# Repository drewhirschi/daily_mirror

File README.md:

# Daily Mirror

Daily Mirror is a small physical camera appliance: press one button, take one
photograph, and upload it to a private chronological gallery.

The current revival keeps the interaction deliberately narrow. There is no
identity recognition, comparison, notes, alignment, or time-lapse generation.

## Repository layout

- `mobile/` — native Expo iOS gallery and account app, with a persistent,
  bounded thumbnail cache. See [`docs/mobile.md`](docs/mobile.md).
  For remote iPhone builds and installation, see the
  [free Tailscale/Xcode bridge guide](docs/tailscale-xcode-bridge.md).
- `packages/api/` — portable TypeScript API client with types generated from
  the Rust server's OpenAPI contract.
- `device/` — new Rust Raspberry Pi client: camera command, GPIO button and
  three LEDs, durable upload queue, and retries.
- `server/` — new NextRS/Axum API, local filesystem storage, React gallery,
  and Docker Compose configuration.
- `processor/` — intermittent Rust face-processing CLI and leased batch runner;
  the inference adapter is intentionally pending model selection.
- `crates/vision-contract/` — shared queue and face-result wire types used by
  the server and processor.
- `src/`, `snapr/`, and `view/` — the original 2022 Python, Rust/OpenCV, and
  React prototypes retained for reference.
- `data/` — photographs and face-recognition experiments from the original
  prototype. New captures do not belong in Git.

## Prototype flow

```text
button -> LED countdown -> ArduCam JPEG -> durable Pi queue
       -> signed upload grant -> local storage or private R2 -> web gallery
```

The device writes a completed JPEG to its queue before uploading. It removes
that file only after the server acknowledges it. A stable capture ID makes
network retries idempotent.

## Start the web server

```sh
cd server
cp .env.example .env
npm install
npm run client:generate
cargo dev
```

See `server/README.md` for the upload API and container setup.

The password-protected production gallery is deployed at
<https://daily-mirror-pearl.vercel.app>.

The planned path from breadboard prototype to an enclosed Pi appliance, R2 and
Vercel deployment, and a later ESP32 port is documented in
[`docs/productization-plan.md`](docs/productization-plan.md).
Deployment commands and the direct-to-R2 upload flow are documented in
[`docs/deployment.md`](docs/deployment.md).
The local Rust processing worker, durable job queue, face landmarks, identity
review workflow, and centered portrait pipeline are documented in
[`docs/face-processing-architecture.md`](docs/face-processing-architecture.md).

## Bring up the Raspberry Pi camera

```sh
cd device
cp .env.example .env
cargo run --release -- capture-once --no-upload
```

After validating the ArduCam output, configure the server URL and test an
upload before wiring GPIO. See `device/README.md` for pin assignments and LED
behavior.

## Inspect the face-processing queue

After setting `DAILY_MIRROR_SERVER_URL`, `DAILY_MIRROR_PROCESSOR_TOKEN`, and
`DAILY_MIRROR_PROCESSING_PIPELINE` in `processor/.env`, run:

```sh
just process-status
```

The leased Rust processing loop is implemented, but `just process` will refuse
to claim production photos until a face inference engine is selected. See
[`processor/README.md`](processor/README.md) and the
[face-processing architecture](docs/face-processing-architecture.md).

## Quality gates

Run `just check` to format-check, lint, generate and validate the typed client,
type-check the gallery, and test all Rust applications. Run
`just install-hooks` once per clone to make the same suite a mandatory local
pre-push hook. GitHub Actions runs it again for every push and pull request,
and production deployment refuses to start until it passes.

The root npm workspace manages mobile and shared TypeScript packages; the
NextRS server keeps its existing generated-client workspace. Run `npm ci` at
the repository root to install mobile dependencies, then `npm run mobile` for
Metro or `npm run ios` on a Mac to build and open the simulator.

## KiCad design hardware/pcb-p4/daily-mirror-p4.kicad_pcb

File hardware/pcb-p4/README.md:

# Daily Mirror custom PCB - A1 component study

Open **daily-mirror-p4.kicad_pro** in KiCad 10. This is an editable starting
project with the connected controls schematic and **64 additional candidate
components** on four new schematic pages and the board. It now has 80 electrical
references plus four mounting holes. The imported main components have no circuit
connections yet; the board has no routed traces. **Do not order this board.**

See [sourcing.md](sourcing.md) for the part choices, 3D-model limitations and
open-reference workflow. [candidate-parts.csv](candidate-parts.csv) records
the new parts and their sources; it is not an order-ready BOM.

An editable, routed Olimex P4 development-board reference is in
[reference/olimex-esp32-p4-devkit](reference/olimex-esp32-p4-devkit).
Open its `ESP32-P4-DevKit_Rev_D1.kicad_pro` separately to inspect the original
connected design. It has not been merged into the Daily Mirror circuit.
The previous A0 files/previews are saved in `revisions/a0`.

## Decisions from this session

- Keep the existing Arducam IMX519 as the camera baseline; preserve the goal of
  16 MP stills. Use a purchased camera module on a ribbon cable. The image
  sensor and lens do not need to be integrated onto the main custom PCB.
- USB-C wall power; a new enclosure designed around the final electronics.
- Cost matters: favor a standard four-layer main board for the P4, common
  stocked components, and assembly on one side where practical. Evaluate total
  assembled cost, including setup and shipping, rather than promotional bare-PCB
  prices. No per-unit budget or production quantity has been specified yet.
- One small four-pin RGB status indicator, plus a momentary capture/pairing button.
- **White-only emitters are preferred** around the perimeter for photographs.
  The three-color CL651-3S modules are optional prototype parts, not a required
  final component. Choose documented white LEDs/modules and their current
  drivers once the brightness, optical layout and power budget are established.
- Snap-in removable diffuser above the light modules. Include an opaque lens
  baffle, room between diffuser and emitters, and space behind the modules for
  a heat-spreading mount. Diffuser material, thickness, gap and clips need an
  optical/mechanical prototype; the current enclosure models are Pi-specific.

## Important processor finding

**The ESP32-P4 is still a candidate, not a confirmed solution for full-resolution
IMX519 capture.** Having a matching MIPI interface does not establish camera support.

Espressif's current ISP header defines `ISP_LL_HSIZE_MAX` as **1920**. Its ISP
driver rejects larger `h_res` values. The IMX519 full image is **4656 x 3496**.
Thus the ordinary P4 ISP processing path cannot process a full-width 16 MP frame.
This is an image-processing-path limit, not proof that every raw CSI/DMA capture
path is impossible. A bypass-and-upload approach would need a sensor driver,
working DMA/buffer handling, exposure/focus control and a server image pipeline.
It has not been implemented or tested here.

The official sensor list does not list a native IMX519 driver. Its Arducam
PIVARIETY entry does not establish support for the user's native IMX519 module.
The community IMX driver project checked lists other IMX sensors, not IMX519;
its results cannot be assumed to apply to this camera.

A packed RAW10 full frame is 20,346,720 bytes (19.40 MiB); a 16-bit-per-pixel
buffer takes 32,554,752 bytes (31.05 MiB), before firmware and other buffers.
Capturing infrequently reduces average throughput, but not those per-frame
buffer requirements. Streaming approaches must be proven separately.

**Next hardware gate:** demonstrate a full-field still from the actual IMX519
on the proposed processor, with usable exposure/focus and successful upload.
If P4 raw capture cannot meet that requirement, select a processor with a
validated IMX519 pipeline before drawing its main circuit. A custom board
does not require a Raspberry Pi, and a P4 has not been chosen merely for size.

Source snapshot: ESP-IDF commit `c712a0dde385d659a1470a136251980d31a70bc1`,
checked September 14, 2026. See [reference/isp-limits.md](reference/isp-limits.md).

## What is actually drawn

| Reference | Circuit | Current choice |
| --- | --- | --- |
| D1 | Common-anode RGB indicator | Project symbol preserves documented pin order: 1 blue, 2 green, 3 common positive, 4 red |
| R1-R3 | One current-limiting resistor per color | 1 kohm provisional; adjust after measuring forward voltage and brightness |
| R5-R7 | Pull each color control high while GPIO is floating | 100 kohm; high = off, low = on |
| SW1 | Normally-open momentary button | Generic 6 mm tactile footprint, 4.3 mm actuator height candidate |
| R4 / C1 | Button pull-up and filter | 10 kohm / 100 nF; approximately 1 ms RC; use firmware debounce as well |
| TP1-TP6 | Future processor/control test access | 3.3 V, ground, blue, green, red, button |
| H1-H4 | Board-only mounting holes | M3 clearance, provisional 92 x 92 mm spacing |

The LED's common positive leg has **no fourth series resistor**. Three separate
color resistors avoid the brightness interactions caused by sharing one resistor.
The 1 kohm starting values cap direct GPIO current below 3.3 mA per channel at
3.3 V; final brightness, GPIO limits and resistor power must be checked against
the chosen parts. This is only the small indicator circuit, not the COB driver.

The RGB symbol follows [the existing wiring record](../../device/README.md),
but the loose LED's view/orientation, lead size and lead order must be confirmed.
The candidate **wide-pin** footprint uses formed leads at 2.54 mm pitch; it is
not a claim that the unbent loose LED has that pitch. The generic button's
mechanical height must also be chosen with the new faceplate.

The board is a **100 x 100 mm, four-copper-layer space study**. None of those
dimensions, mounting holes or layer rules is a final manufacturing specification.
The PCB now contains the imported candidate footprints, including eight white
emitters. The camera faceplate clearance is still a drawing guide; the separate
camera module, cable, diffuser and enclosure have not been mechanically modeled.
The 3D preview represents these placed components; five package types use explicitly
approximate models. See the sourcing notes before using this for mechanical fit.

## Existing CL651-3S prototype light modules

The final board can use white-only parts instead. The notes below apply only
if the already-owned three-color modules are used for prototype measurements.

The supplied photo and the manual linked from the exact
[Temu listing](https://www.temu.com/goods.html?goods_id=606385509136562&sku_id=99388093393455)
identify a three-color, common-negative COB module. The manual explicitly maps:

| Pad marking | Seller's stated function |
| --- | --- |
| `B+` | White positive |
| `W+` | Blue positive |
| `R+` | Red positive |
| `-` | Shared negative |

This unusual B/W assignment should be checked at low current on a current-limited
bench supply before wiring a batch. Only white and negative will be used;
unused red/blue positives stay unconnected.

The listing/manual states **3.2-3.7 V** and warns of heating at 3.7 V. It provides
**no rated current, pulse current, pulse width, thermal resistance, CRI or CCT**.
It is not a complete electrical datasheet. Do not substitute its broad listing
category `<=36 V` for the actual operating voltage.

Plan a controlled-current path for each white module, with default-off enable
and a bounded illumination time. Do not drive COB modules from GPIO, connect
them directly to USB's 5 V, or infer a current limit from voltage alone. Do not
parallel bare modules behind one driver without a validated current-sharing scheme.
The appropriate buck/linear topology, current sense resistor, module count,
connector, copper area and USB supply rating remain unresolved.

These parts already have their own substrate. The likely integration is short
two-wire connections to modules mounted around the faceplate/perimeter, with
control electronics on the main PCB. Direct mechanical/electrical attachment
to the main board needs measured pad positions, mounting holes and a thermal
design. No guessed CL651-3S solder footprint is included.

### Flash timing and diffuser

Short duty cycles reduce average heat: `average electrical power = V * I *
on-time * flashes-per-second` for constant rectangular pulses. Peak junction
temperature and safe pulse current still matter; average power alone does not
establish safety. Repeated presses and a stuck-on software state must be tested.
No pulse overdrive is assumed without a manufacturer rating.

The IMX519 is a rolling-shutter camera. Start with steady white illumination
through the full frame exposure/readout window, then characterize the shortest
uniform pulse from actual captured images. Avoid unsynchronized PWM during
capture. Test for bands, face shadows, clipping, diffuser hot spots, lens flare
and enclosure temperature at the maximum intended repeat rate.

Record current, measured light output and duration before deciding whether a
small heat spreader is enough. Keep diffuser clips clear of the thermal path.

## What the main circuit still needs

- Camera-proven processor, package/revision and memory capacity.
- For a P4 design: external flash, reference crystal, core regulator, PHY and
  other supplies/decoupling, reset/boot circuitry and programming access. Use
  Espressif's revision-v3-or-later reference; older revisions differ electrically.
- Wi-Fi/BLE companion and antenna layout if using P4. ESP32-C6-MINI-1 with SDIO
  is the reference direction; P4 itself does not contain a Wi-Fi/BLE radio.
- USB-C connector, CC handling, input protection, regulator and current budget.
  Two CC pull-downs establish a sink attachment but do not by themselves authorize
  a 3 A load. Detect the source's available current or negotiate PD as required.
- Exact Arducam module SKU/revision and ribbon. Pi-style connectors can be 15-pin
  1 mm or 22-pin 0.5 mm. Confirm connector-side pin numbering, contacts, supply,
  controls, level shifting and cable orientation before assigning the footprint.
- CSI differential pairs routed against the chosen fabricator's stackup and
  Espressif's guidelines; impedance is not established by arbitrary trace widths.
- Flash/illumination driver and any local storage required for failed uploads.

The phone experience is firmware/app work too: BLE discovery while pairing,
authenticated ownership setup, transfer of Wi-Fi credentials, association and
account registration, then normal capture/upload. Add long-press recovery,
factory reset, signed updates and upload retry. KiCad does not implement this.
The existing Pi program invokes `rpicam-still`; that part cannot run unchanged
on the P4. Backend protocols and device states can be reused where applicable.

## KiCad setup and working together

KiCad **10.0.6** was installed without its library packages. The matching official
Arch packages (`kicad-library` and `kicad-library-3d`, 10.0.6-1) were downloaded,
their signatures verified against the installed Arch keyring, and extracted to:

`/home/drew/.local/share/kicad/10.0/official-10.0.6`

This per-user install avoids the system installer's password requirement. It
does not register those two library packages with pacman. KiCad's global library
table references and `KICAD10_*` paths were updated. The previous settings are in:

`/home/drew/.config/kicad/10.0/before-daily-mirror-20260914-214132`

The dangling default reference to a nonexistent optional design-block library
was also removed; its original table is in that backup. Design blocks are not
needed for this project.

Restart KiCad once if it was already open. Then:

1. **File > Open Project** and select `daily-mirror-p4.kicad_pro` in this directory.
2. Open the `.kicad_sch` for the architecture and control circuit.
3. Open the `.kicad_pcb`; enable `User.Drawings` to see the reserved areas.
4. Use **View > 3D Viewer** to inspect the placed candidate parts.

The current 3D render is `output/board-3d.png`. The STEP assembly in
`output/daily-mirror-a0.step` contains the current board and the placed component
models, and can be opened in mechanical CAD for enclosure work. Neither includes
the unselected processor, camera module, power connectors or white emitters.

### Reading the design

The schematic describes electrical connections. Green lines are wires in that
diagram; repeated net names identify the same electrical connection without
drawing a long line across the page. The PCB shows real component locations and
solder pads. Its connections become copper **traces** routed between pads;
this initial board has no routed traces yet. In the PCB editor, thin ratsnest
lines can show which pads still need connections; those are guides, not copper.
The 3D viewer shows physical models, not schematic symbols or ratsnest lines.

| Label | Meaning |
| --- | --- |
| J1, J2 | Connectors, such as camera ribbon or USB |
| U1, U2 | Integrated circuits/chips; exact function depends on the part |
| R1, R2 | Resistors |
| C1, C2 | Capacitors; often resemble tiny resistors |
| D1 | Diode or LED |
| SW1 | Switch/button |
| TP1 | Test point |

For a sourced part, check three separate CAD representations: its schematic
symbol (electrical pins), footprint (solder pads and holes), and STEP/3D model
(physical shape). Matching physical shape alone does not prove the pin mapping
or circuit works. Use exact manufacturer part numbers and package drawings.

### Making a physical unit

PCB fabrication makes the patterned copper board. PCB assembly adds and solders
the purchased components. An assembly order typically needs Gerbers/drill files,
a bill of materials with exact part numbers, and placement/orientation data.
Fabricators do not print silicon image sensors or lenses. A camera module can
be purchased separately and connected after board assembly.

JLCPCB offers an assembly parts library and sourcing/consignment options;
PCBWay offers turnkey, partial-turnkey and customer-supplied component assembly.
Stock, exact packages and service eligibility must be checked before choosing
the final bill of materials. Firmware flashing and functional testing require
their own agreed process; soldering the board does not establish that it works.

- [DigiKey CAD models](https://www.digikey.com/en/product-highlight/a/accelerated-designs/ultra-librarian)
- [KiCad 10 PCB and 3D documentation](https://docs.kicad.org/10.0/en/pcbnew/pcbnew.html)
- [JLCPCB bill of materials requirements](https://jlcpcb.com/help/article/bill-of-materials-for-pcb-assembly)
- [JLCPCB parts sourcing](https://jlcpcb.com/help/article/how-to-build-your-own-parts-library-in-jlcpcb)
- [PCBWay component sourcing](https://www.pcbway.com/pcb_prototype/Electronic_Components.html)

There is no callable KiCad MCP in this session. We can edit the native files
and use KiCad CLI for validation and previews. Close the affected editor before
external edits and reopen it afterward; do not assume live reload. For edits
made in the schematic editor, **Update PCB from Schematic (F8)** transfers changes.
The `.kicad_pro` file is the project, `.kicad_sch` is the circuit, and
`.kicad_pcb` is the physical board.

Small project-local symbol, footprint and 3D libraries make the study portable.
The generator refuses to overwrite an existing design. Interactive KiCad files
are the source of truth once editing begins. To reproduce the initial study in
a separate directory:

```sh
python build_starter.py --output /tmp/daily-mirror-pcb-study
```

## Checks

See [output/validation.json](output/validation.json) for the final counts.
The controls schematic still has zero ERC violations and its nine nets match
the board pads. All 80 schematic component pin-number sets match the footprints,
with J2's additional mechanical mounting tabs explicitly accounted for. All 74
placed model references resolve. No component courtyards overlap.

The whole project has **377 ERC findings** from unconnected/undriven candidate
pins and **96 DRC findings** (USB pad nets/connector hole clearance and silkscreen
size/overlaps). The 21 unrouted controls connections remain; because the new
circuits have no assigned nets, that number does not count their future routing.
No Daily Mirror Gerbers, assembly order or firmware release has been produced.

## Sources

- [Espressif P4 reference board](https://docs.espressif.com/projects/esp-dev-kits/en/latest/esp32p4/esp32-p4-function-ev-board/user_guide.html): P4/C6 architecture.
- [P4 schematic guidance](https://docs.espressif.com/projects/esp-hardware-design-guidelines/en/latest/esp32p4/schematic-checklist-esp32p4.html): revision changes and support circuitry.
- [P4 layout guidance](https://docs.espressif.com/projects/esp-hardware-design-guidelines/en/latest/esp32p4/pcb-layout-design-esp32p4.html): signal and power layout.
- [Espressif sensor support](https://github.com/espressif/esp-video-components/tree/master/esp_cam_sensor): supported sensors.
- [Arducam IMX519 documentation](https://docs.arducam.com/Raspberry-Pi-Camera/Native-camera/16MP-IMX519/): resolution, RAW formats and rolling shutter.
- [Community IMX driver project](https://github.com/mushBrainDave/esp32-p4-imx-camera): context only; not an IMX519 compatibility claim.
- [Raspberry Pi camera documentation](https://www.raspberrypi.com/documentation/accessories/camera.html): connector families.
- [Seller's LED manual](reference/cl651-3s-manual.pdf): voltage, terminal labels and heat warning; no current rating.

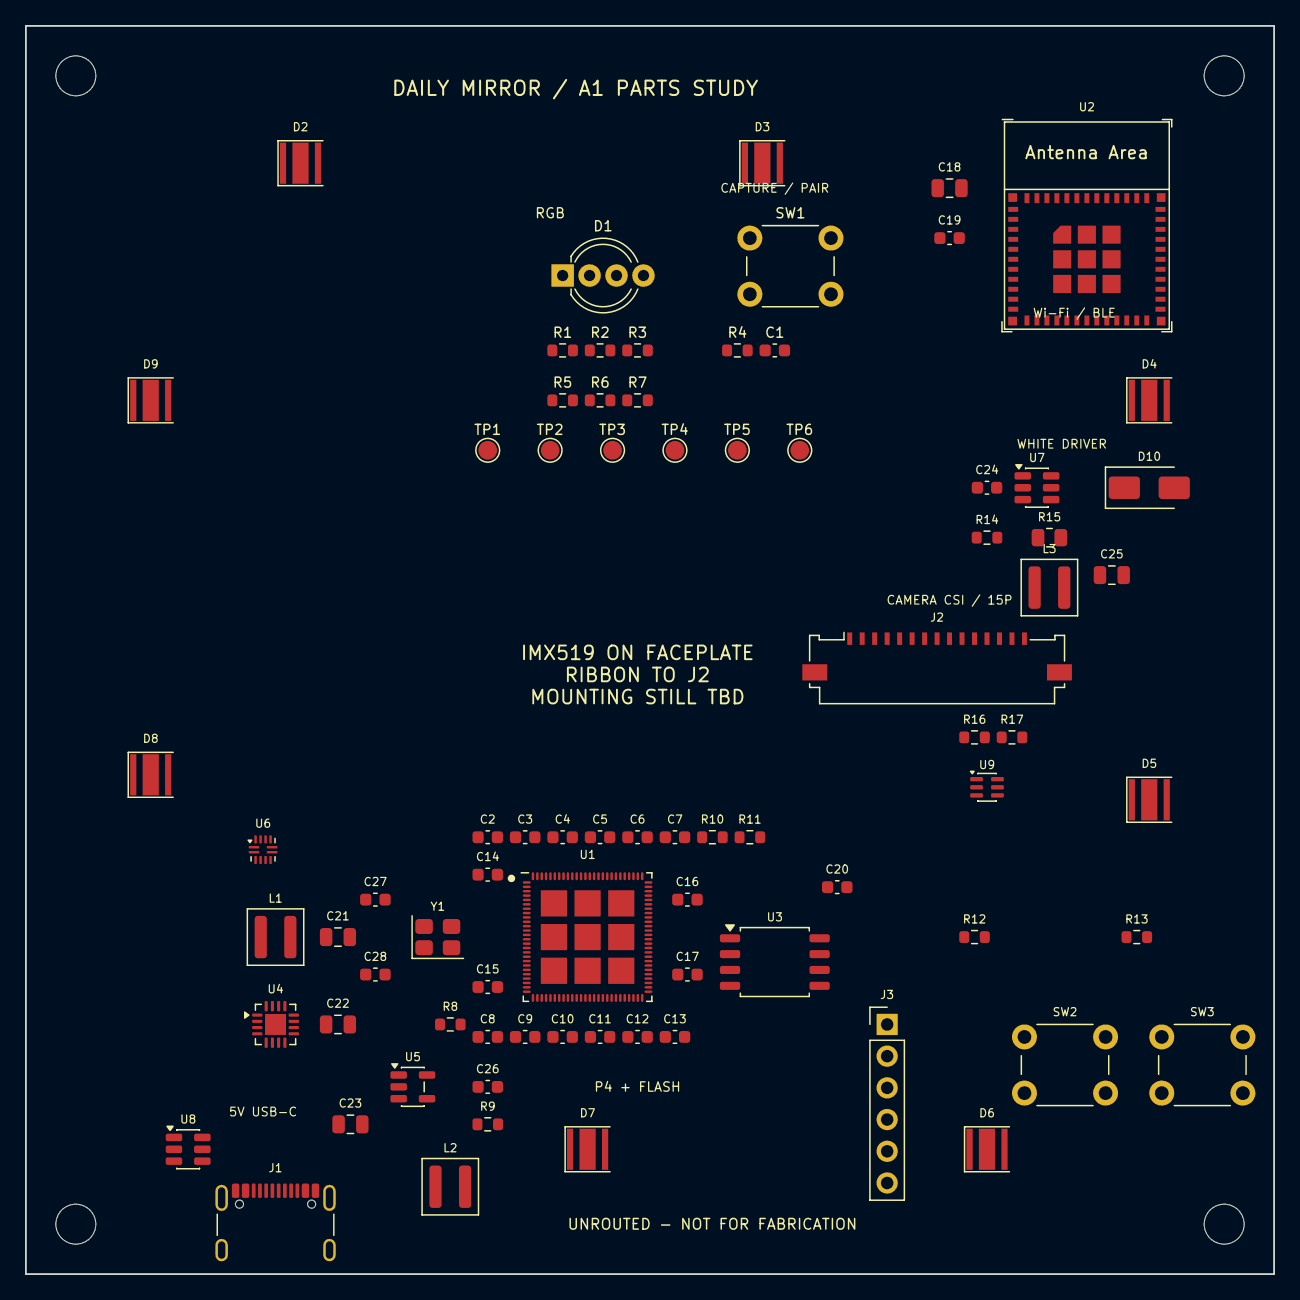
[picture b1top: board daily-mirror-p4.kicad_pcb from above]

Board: 4 copper layers, 100.0 x 100.0 mm, 84 parts (0 on the bottom side), 9 nets, no tracks yet.

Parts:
C1, C2, C3, C4, C5, C6, C7, C8, C9, C10, C11, C12, C13, C14, C15, C16, C17, C19, C20, C24: 100nF; C_0603_1608Metric
C18, C21, C22, C23: 10uF; C_0805_2012Metric
C25: 1uF; C_0805_2012Metric
C26: 22pF; C_0603_1608Metric
C27, C28: TUNE pF; C_0603_1608Metric
D1: RGB common anode; LED_D5.0mm-4_RGB_Wide_Pins
D2, D3, D4, D5, D6, D7, D8, D9: White 5000 K / CRI90; LED_Cree-XP-G
D10: SS16-E3/61T; D_SMA
H1, H2, H3, H4: MountingHole_3.2mm_M3
J1: USB-C / 5 V; USB_C_Receptacle_GCT_USB4105-xx-A_16P_TopMnt_Horizontal
J2: Pi-style CSI camera - 15 pin; Molex_200528-0150_1x15-1MP_P1.00mm_Horizontal
J3: Service UART / boot; PinHeader_1x06_P2.54mm_Vertical
L1, L2: 2.2 uH; L_Coilcraft_XAL4020-XXX
L3: 10 uH; L_Coilcraft_XAL4040-XXX
R1, R2, R3: 1k (start); R_0603_1608Metric
R4, R12, R13: 10k; R_0603_1608Metric
R5, R6, R7, R14: 100k; R_0603_1608Metric
R8, R9: 499k; R_0603_1608Metric
R10, R11: 4.02k; R_0603_1608Metric
R15: 2 ohm; R_0805_2012Metric
R16, R17: 2.2k; R_0603_1608Metric
SW1: Momentary NO; SW_PUSH_6mm_H4.3mm
SW2: RESET; SW_PUSH_6mm_H4.3mm
SW3: BOOT; SW_PUSH_6mm_H4.3mm
TP1: +3V3; TestPoint_Pad_D1.5mm
TP2: GND; TestPoint_Pad_D1.5mm
TP3: STATUS_B_N; TestPoint_Pad_D1.5mm
TP4: STATUS_G_N; TestPoint_Pad_D1.5mm
TP5: STATUS_R_N; TestPoint_Pad_D1.5mm
TP6: USER_BUTTON_N; TestPoint_Pad_D1.5mm
U1: ESP32-P4NRW32X; ESP32-P4
U2: ESP32-C6-MINI-1-N4; ESP32-C6-MINI-1
U3: W25Q128JVSIQ; SOIC-8_5.3x5.3mm_P1.27mm
U4: TPS62132RGTR; VQFN-16-1EP_3x3mm_P0.5mm_EP1.68x1.68mm
U5: TLV62569DBVR; SOT-23-5
U6: TUSB320IRWBR; Texas_X2QFN-12_1.6x1.6mm_P0.4mm
U7: TPS61165DBVR; SOT-23-6
U8: USBLC6-2SC6; SOT-23-6
U9: TPS22919DCKR; SOT-363_SC-70-6
Y1: 40 MHz / 10 pF; Crystal_SMD_3225-4Pin_3.2x2.5mm

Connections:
/+3V3: D1.3, R4.1, R5.1, R6.1, R7.1, TP1.1
/GND: C1.2, SW1.2, TP2.1
/LED_B_K: D1.1, R1.2
/LED_G_K: D1.2, R2.2
/LED_R_K: D1.4, R3.2
/STATUS_B_N: R1.1, R5.2, TP3.1
/STATUS_G_N: R2.1, R6.2, TP4.1
/STATUS_R_N: R3.1, R7.2, TP5.1
/USER_BUTTON_N: C1.1, R4.2, SW1.1, TP6.1

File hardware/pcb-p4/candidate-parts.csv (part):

ref,value,manufacturer,mpn,footprint,sheet,status,source,note
U1,ESP32-P4NRW32X,Espressif,ESP32-P4NRW32X,ESP32-P4,processor,Candidate; wiring and qualification pending,https://documentation.espressif.com/esp32-p4_datasheet_en.html,Current X / rev3+ symbol. IMX519 full-resolution path unproven. 32 MB in-package PSRAM; external flash required.
U2,ESP32-C6-MINI-1-N4,Espressif,ESP32-C6-MINI-1-N4,ESP32-C6-MINI-1,processor,Candidate; wiring and qualification pending,https://www.espressif.com/sites/default/files/documentation/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,Wi-Fi/BLE companion. SDIO/ESP-Hosted integration pending. Antenna needs copper/component keepout.
U3,W25Q128JVSIQ,Winbond,W25Q128JVSIQ,SOIC-8_5.3x5.3mm_P1.27mm,processor,Candidate; wiring and qualification pending,https://www.winbond.com/resource-files/w25q128jv_dtr%20revc%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,16 MiB external SPI flash; boot flash voltage and strapping pending.
J2,Pi-style CSI camera - 15 pin,Molex,2005280150,Molex_200528-0150_1x15-1MP_P1.00mm_Horizontal,processor,Candidate; wiring and qualification pending,https://www.molex.com/en-us/products/part-detail/2005280150,"Bottom-contact, 1 mm pitch. Confirm actual Arducam module/ribbon contact side and pinout before wiring."
Y1,40 MHz / 10 pF,Abracon,ABM8-40.000MHZ-10-1-U-T,Crystal_SMD_3225-4Pin_3.2x2.5mm,processor,Candidate; wiring and qualification pending,https://abracon.com/Support/SPICE/Resonators/ABM8-Series%20P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,Manufacturer test report gives +/-10 ppm. Ordering availability and temperature specification need confirmation; generic package model.
U4,TPS62132RGTR,Texas Instruments,TPS62132RGTR,VQFN-16-1EP_3x3mm_P0.5mm_EP1.68x1.68mm,power,Candidate; wiring and qualification pending,https://www.ti.com/product/TPS62132,"Fixed 3.3 V, 3 A main buck. Inductor/output network and load budget pending."
U5,TLV62569DBVR,Texas Instruments,TLV62569DBVR,SOT-23-5,power,Candidate; wiring and qualification pending,https://www.ti.com/product/TLV62569,"P4 core buck. Use rev3+ feedback/control circuit, not a fixed generic 1.1 V assumption."
U6,TUSB320IRWBR,Texas Instruments,TUSB320IRWBR,Texas_X2QFN-12_1.6x1.6mm_P0.4mm,power,Candidate; wiring and qualification pending,https://www.ti.com/product/TUSB320/part-details/TUSB320IRWBR,5 V Type-C source-current detection. Configure sink. Not a PD controller; gate load to advertised current. Stock availability not confirmed.
U8,USBLC6-2SC6,STMicroelectronics,USBLC6-2SC6,SOT-23-6,power,Candidate; wiring and qualification pending,https://www.st.com/en/protection-devices/usblc6-2.html,USB data-line ESD protection; additional VBUS/CC protection design pending.
U9,TPS22919DCKR,Texas Instruments,TPS22919DCKR,SOT-363_SC-70-6,power,Candidate; wiring and qualification pending,https://www.ti.com/product/TPS22919,Camera power switch candidate; confirm camera module supply and startup current.
J1,USB-C / 5 V,GCT,USB4105-GF-A,USB_C_Receptacle_GCT_USB4105-xx-A_16P_TopMnt_Horizontal,power,Candidate; wiring and qualification pending,https://gct.co/connector/USB4105,Select exact stake length/order suffix with board thickness; input load protection/inrush circuitry pending.
J3,Service UART / boot,Generic,TBD 1x06 2.54 mm header,PinHeader_1x06_P2.54mm_Vertical,power,Candidate; wiring and qualification pending,https://gitlab.com/kicad/libraries/kicad-footprints,Service pinout not assigned; prefer production test pads in final design.
SW2,RESET,Generic,TBD 6 mm tactile,SW_PUSH_6mm_H4.3mm,power,Candidate; wiring and qualification pending,https://gitlab.com/kicad/libraries/kicad-footprints,Generic body; choose exact switch force/actuator height for enclosure.
SW3,BOOT,Generic,TBD 6 mm tactile,SW_PUSH_6mm_H4.3mm,power,Candidate; wiring and qualification pending,https://gitlab.com/kicad/libraries/kicad-footprints,Generic body; choose exact switch force/actuator height for enclosure.
U7,TPS61165DBVR,Texas Instruments,TPS61165DBVR,SOT-23-6,lighting,Candidate; wiring and qualification pending,https://www.ti.com/product/TPS61165,"Constant-current boost candidate. 1.2 A is switch rating, not available LED output current. Tentative eight-series / 100 mA for initial optical study only."
D10,SS16-E3/61T,Vishay,SS16-E3/61T,D_SMA,lighting,Candidate; wiring and qualification pending,https://www.vishay.com/en/product/88746/,"Boost rectifier candidate; calculate peak current, losses and reverse voltage."
D2,White 5000 K / CRI90,Cree LED,XPGDWT-U1-0000-00J3E,LED_Cree-XP-G,lighting,Candidate; wiring and qualification pending,https://downloads.cree-led.com/files/ds/x/XLamp-XPG3.pdf,"Plain white XP-G3. Qty eight provisional. Shared XP-G footprint and package STEP are candidates, not an exact manufacturer XP-G3 model. Thermal pad electrically isolated from LED; heat-spreading copper required."
D3,White 5000 K / CRI90,Cree LED,XPGDWT-U1-0000-00J3E,LED_Cree-XP-G,lighting,Candidate; wiring and qualification pending,https://downloads.cree-led.com/files/ds/x/XLamp-XPG3.pdf,"Plain white XP-G3. Qty eight provisional. Shared XP-G footprint and package STEP are candidates, not an exact manufacturer XP-G3 model. Thermal pad electrically isolated from LED; heat-spreading copper required."
D4,White 5000 K / CRI90,Cree LED,XPGDWT-U1-0000-00J3E,LED_Cree-XP-G,lighting,Candidate; wiring and qualification pending,https://downloads.cree-led.com/files/ds/x/XLamp-XPG3.pdf,"Plain white XP-G3. Qty eight provisional. Shared XP-G footprint and package STEP are candidates, not an exact manufacturer XP-G3 model. Thermal pad electrically isolated from LED; heat-spreading copper required."
D5,White 5000 K / CRI90,Cree LED,XPGDWT-U1-0000-00J3E,LED_Cree-XP-G,lighting,Candidate; wiring and qualification pending,https://downloads.cree-led.com/files/ds/x/XLamp-XPG3.pdf,"Plain white XP-G3. Qty eight provisional. Shared XP-G footprint and package STEP are candidates, not an exact manufacturer XP-G3 model. Thermal pad electrically isolated from LED; heat-spreading copper required."
D6,White 5000 K / CRI90,Cree LED,XPGDWT-U1-0000-00J3E,LED_Cree-XP-G,lighting,Candidate; wiring and qualification pending,https://downloads.cree-led.com/files/ds/x/XLamp-XPG3.pdf,"Plain white XP-G3. Qty eight provisional. Shared XP-G footprint and package STEP are candidates, not an exact manufacturer XP-G3 model. Thermal pad electrically isolated from LED; heat-spreading copper required."
D7,White 5000 K / CRI90,Cree LED,XPGDWT-U1-0000-00J3E,LED_Cree-XP-G,lighting,Candidate; wiring and qualification pending,https://downloads.cree-led.com/files/ds/x/XLamp-XPG3.pdf,"Plain white XP-G3. Qty eight provisional. Shared XP-G footprint and package STEP are candidates, not an exact manufacturer XP-G3 model. Thermal pad electrically isolated from LED; heat-spreading copper required."
D8,White 5000 K / CRI90,Cree LED,XPGDWT-U1-0000-00J3E,LED_Cree-XP-G,lighting,Candidate; wiring and qualification pending,https://downloads.cree-led.com/files/ds/x/XLamp-XPG3.pdf,"Plain white XP-G3. Qty eight provisional. Shared XP-G footprint and package STEP are candidates, not an exact manufacturer XP-G3 model. Thermal pad electrically isolated from LED; heat-spreading copper required."
D9,White 5000 K / CRI90,Cree LED,XPGDWT-U1-0000-00J3E,LED_Cree-XP-G,lighting,Candidate; wiring and qualification pending,https://downloads.cree-led.com/files/ds/x/XLamp-XPG3.pdf,"Plain white XP-G3. Qty eight provisional. Shared XP-G footprint and package STEP are candidates, not an exact manufacturer XP-G3 model. Thermal pad electrically isolated from LED; heat-spreading copper required."
L1,2.2 uH,Coilcraft,XAL4020-222MEC,L_Coilcraft_XAL4020-XXX,power,Candidate; wiring and qualification pending,https://www.coilcraft.com/en-us/products/power/shielded-indu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,Electrical value and current/temperature margin provisional; package imported from KiCad.
L2,2.2 uH,Coilcraft,XAL4020-222MEC,L_Coilcraft_XAL4020-XXX,power,Candidate; wiring and qualification pending,https://www.coilcraft.com/en-us/products/power/shielded-indu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,Electrical value and current/temperature margin provisional; package imported from KiCad.
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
